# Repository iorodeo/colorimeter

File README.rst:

Colorimeter
-----------

Design files, software and firmware for IO Rodeos's open source (hardware &
software) scientific colorimeter kit for educators, students and DIY
scientists. Colorimeters are analytical devices commonly used in science labs to measure
the concentration of a solution from its light absorbing properties.
Colorimeters are extremely useful and flexible lab instruments for a wide range
of science education labs. 

This packages contains:

* Design files for the colorimeter Electronic Kicad) and Mechanical (py2scad) components.

* Arduino firmware and Python serial library for communicating the colorimeter.  

* A suite of software (w/GUI) for taking measurements with the colorimeter - e.g. 
  measuring transmittance and absorbance, generating standard curves, and  measuring 
  the concentration of solutions.

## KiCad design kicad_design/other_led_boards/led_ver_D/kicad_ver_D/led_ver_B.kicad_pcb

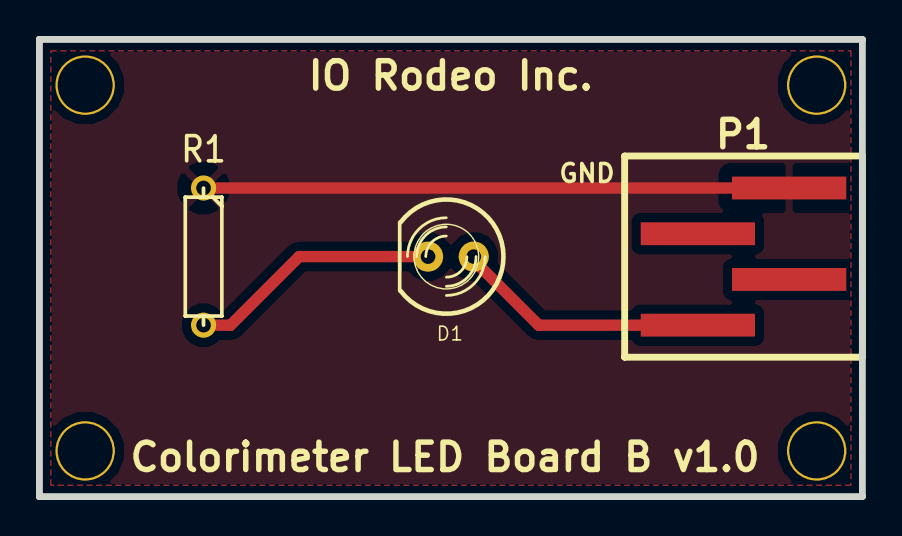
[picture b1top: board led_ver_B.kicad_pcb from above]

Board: 2 copper layers, 45.7 x 25.4 mm, 7 parts (0 on the bottom side), 3 nets.

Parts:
D1: LED; LED-5MM
M1, M2, M3, M4: MOUNT_HOLE_4_40
P1: CONN_4; smt
R1: 40; R3

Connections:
/Blue: D1.1, P1.1
GND: P1.4, R1.1
unnamed: D1.2, R1.2

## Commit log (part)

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2011-12-31 Project creation.
2011-12-31 Added firmware.
2012-01-04 New rgb led design.
2012-01-05 Added Kicad design for the Arduino shield for the colorimeter.
2012-01-07 Added KiCad footprints for two surface mount components.
2012-01-10 Finished designing Arduino shield PCB for the colorimeter.
2012-01-11 Created new version 1.1 of the color sensor PCB. New version has a 5x2 header replacing the 6x2 header. Routed the shield board and re-routed sensor v1.1. Created gerber files.
2012-01-12 Added BOMs for all three boards.
2012-01-14 Enclosure changes - resized holes and added cuvette holder.
2012-01-17 Worked on the enclosure designs. Started to add in the new sliding cover.
2012-01-17 Worked on Colorimeter class.
2012-01-18 Worked on py2scad enclosure design.
2012-01-18 Worked on colorimeter class. Finished getFrequency and getTransmission methods.
2012-01-19 Finished version 2 of the new colorimenter enclosure design.
2012-01-20 Finished writing absorbance calculation. Next up calibration.
2012-01-27 Added white channel. Worked on calbiration.
2012-01-30 Minor work on colorimeter. Played around to see if I could get LCD to stop flashing when the colorimeter take measurements.
2012-02-01 Finished Colorimeter class. Preliminary test suggest that it is working.
2012-02-02 Added class template for colorimeter data.
2012-02-02 Started working on SerialHandler class for handling serial communications with host computer.
2012-02-03 Finished serial interface - both for firmware and host. Wrote a simple gui for working with the device.
2012-02-03 Added IO pins for arduino uno shield.
2012-02-03 Created python package for colorimeter serial interface.
2012-02-04 Minor changes to python software.
2012-02-06 Added firmware test functions.
2012-02-07 Fixed bug in firmware which caused white values to be the same as the red values. Added color selection checkboxes to GUI. Added number of samples line edit to GUI.
2012-02-10 Changes to the sensor and LED boards to replace the terminal blocks with surface mount components.
2012-02-10 Version 2 of the colorimeter. Removed alot of the components that are not necessary to make a very basic breakout board.
2012-02-10 version 2p0 gerber files for sensor, led and shield boards.
2012-02-11 New project: Nano colorimeter shield
2012-02-15 Fixed design bugs. Still need to remake dxf files, etc.
2012-02-15 Added kicad missing kicad modules.
2012-03-03 Modified both sensor and LED boards to a new surface mount 4-pin male header instead of the poke home connectors. New gerber files v2p1 for both boards.
2012-03-19 Fixed spelling error on GUI text label.
2012-03-21 Added an annotated parts list for the enclosure.
2012-03-21 Added a new file for the concentration GUI.
2012-04-10 Added prototype of colorimater plotting GUI.
2012-04-10 Finished mockup of concentration GUI.
2012-04-17 Added parts layout for instructables.
2012-04-17 Separated plotting and concentration guis (mockups) from the other parts.
2012-04-17 Modified colorimeter_gui so that default serial port is automatically selected based on platform.
2012-05-30 Created slight offset in shrouded header hole position for sensor pcb.
2012-05-30 Modified inner panel slot position so that it is better aligned with the led and sensor.
2012-06-19 Working version of Plot GUI
2012-06-20 Modified colorimeter plot gui so that matplotlib backend is specified.
2012-06-20 Worked on packaging of python serial interface and various GUI's.
2012-06-20 Added temporary work around to figlegend issue on the plotting gui.
2012-06-25 Added silk screen markings to the arduino sheild. Changed the silk screen marking on the LED board - modified version number.
2012-06-25 Modified inner panel LED cable hole size. Remade laser cutting files. Restructured project file slightly.
2012-06-27 Modified firmware so that it works with Arduion versions both > 1.0 and < 1.0.
2012-07-02 Worked on measurement GUI.
2012-07-02 Further work on measurement gui.
2012-07-04 Work on measurement GUI. Added ability to test solution data from the default and user directories.
2012-07-04 Worked on context menus for tablewidget and copy, delete, edit functionality.
2012-07-05 Work on ploting function for measurement GUI.
2012-07-05 Cleaned up a a bit.
2012-07-06 Worked on ctl-c and context menu functionality for measurement GUI data tables. Fixed issue with basic GUI plotting.
2012-07-06 Modified fit used in colorimeter plot GUI so that it is constained to go through zero.
2012-07-07 Worked on measurement GUI plotting. Added live updating of plot - to new measurements and update of sample labels. Added computation of test solution coefficients from data files. Worked on delete fu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
2012-07-15 Worked on measurement and plotting gui. Added validator to plotting gui data table. Added pkg_resource stuff to measurement software - so that data files are found properly.
2012-07-16 Worked on export/import for test solution data sets.
2012-07-16 Worked on import/export of data sets.
2012-07-16 Worked on data import export. Fixed some issues with widget enable order on plot GUI.
2012-07-16 More work on export/import between plotting gui and measurement gui.
2012-07-16 Turned off development (fake it) mode for plotting gui.
2012-07-16 Modified how test solutions will be edited for both measurement and plot (standard curve) GUIs.
2012-07-16 Added led to data saved by plot and measurement GUI. LED is also now set when data is loaded into the plot GUI.
2012-07-17 Worked on unifiying handling of the data table widgets used in the plot and measurement GUIs.
2012-07-18 Worked on unifying the colorimeter GUI components.
2012-07-19 Worked on unifying the plotting and measurement GUIs.
2012-07-19 Further work on unifying the plotting and measurement programs.
2012-07-20 Worked on basic program. Fixed some issues with bar chart as it didn't reflect the current led selection. Made it so that bar chart updates with any changes to GUI and closes when GUI is closed.
2012-07-24 Work on all three programs - basic, plot, and measurement. Fixed issues with serial interface. Made modifications to firmware - so that errors can be more easily caught.
2012-07-24 Work on unifying basic program with the plotting and measuremnt programs.
2012-07-24 Further work on unify the basic program with the other two - plotting and measurement. Some minor changes to the device firmware.
2012-07-24 Finished unifying the basic program with the plotting and measurement programs.
2012-07-24 Started rearranging directory structure.
2012-07-24 More changes to python package sturcture.
2012-07-24 More work rearranging python package.
2012-07-25 Worked on test solution dialog.
2012-07-25 Finished test solution edit and import dialogs.
2012-07-25 Worked on auto creation of user data directory.
2012-07-26 Finished adding automatic user data directory creation.
2012-07-26 Fixed issue with setup.py.
2012-07-26 Moved setting of matplotlib backend to single module.
2012-07-26 Fixed issue with package_data in setup.py file.
2012-07-26 Fixed issue with starting position on windows.
2012-07-26 Added default test solutions.
2012-07-26 Modified so that default test solutions show up in the import dialog but not in the edit dialog.
2012-07-26 Modified import export so that it will work with pyinstaller as well with setup_tools.
2012-07-26 Added About dialogs w/ version number information. Set fake measure flag to False. Prettified saving for basic program.
2012-07-26 Modified the about text message.
2012-07-26 Fixed bug which effected changing test solutions in the measurement GUI.
2012-07-27 Added startup dialog.
2012-07-27 Fixed some python packaging issues and added colorimeter-main script for starting the startup dialog.
2012-07-27 Fixed some issues with using startup dialog which cause problems on windows.
2012-07-27 Fixed issues with serial connection errors on windows.
2012-07-27 Added required libraries to project - so users don't need to deal with this.
2012-07-27 Added top level readme to project.
2012-07-27 Modified readme.
2012-07-27 Modified top level README. Modified INSTALL.txt for python package.
2012-07-27 Removed scipy as requirement from python installation instructions.
2012-09-13 Cleaned up laser cutting files.
2012-09-13 Added BOMs and clean up laser cutting files.
2012-12-19 Worked on adding a nonlinear fit to colorimeter software.
2012-12-20 Added nonlinear fitting capability to plotting and measurement programs.
2012-12-20 Added method to color sensor class to allow selecting the sensors frequency scaling. Changed the default frequency scaling from 20% to 100% to enable measurement of higher concentrations. Set python 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
2012-12-20 Added API test kit data (ammonian, nitrate, nitrite) to the default data sets.
2012-12-21 Added copy of pyinstaller .spec file for compiling stand alone binaries. Currently works with pyinstaller 1.5 haven't tested upgrade to pyinstaller 2.0.
    Added cheap hack to deal with missing item from hiddenimports in scipy hook when
    using pyinstaller.
2012-12-21 Changed name in pyinstaller .spec file.
2012-12-21 Add error dialog to measurement program for the case where the users is using a nonlinear fit and the measurement falls outside of the calibration range - basically disallow extrapolation.
2013-02-22 Added inkscape files for sled and tuxcase top.
2013-04-14 Added Kicad design files for additional LED boards. Version B (single LED) and Version C (two LEDs).
2013-04-16 Worked on added ability to handle custom single LED PCB. Updateded firmware, serial libraray, and worked on updating GUI. Basic program has been modified, still need to finish modifiying the plotting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
2013-04-21 Worked on adding new custom LED mode to plotting and measurement programs.
2013-04-21 Finished modifications to software so that the colorimeter can be used with the 'custom' LED PCB.
2013-04-24 Changed default number of samples. Fixed bug which occured when switching to custom LED mode when there was no test solution data avialable.
2013-04-25 Added lineEdit for setting number for samples to the plot and measure programs.
2013-04-26 Added significant digits options.
2013-04-26 Fixed bug in plot.py which was caused by adding significant digits option.
2013-08-29 Moved .pde to .ino
2013-08-30 Began work adding modes for using both custom led board version B and C.
2013-08-31 Worked on adding custom led option for version c pcb.
2013-09-03 Worked on adding new ver C PCB mode. Refactoring how this is handled.
2013-09-11 Added pin definitions for BLE shield.
2013-10-26 Worked on additing ability to use version c pcb to plottin program. Modified GUI and made changes so that is will at least open with the new data structures.
2013-10-26 Modified plot.py so that measurements are working with the new data structures.
2013-10-26 Finished modificatinos to plot.py so that it works with the version c pcb.
2013-10-27 Finished modifications to measure.py so that it will work with version c pcb.
2013-10-27 Fixed issue with colormode setting.
2013-12-30 Fixed bug effecting saveing and loading data sets
2013-12-31 Added raise_ after to show to various GUI apps so they come to the front in Mac OS.
2014-05-15 New version D design with PLCC 5050 LED and transistor switch for higher voltages. Note, still need to rename some files.
2014-05-15 Changed some file names.
2014-05-15 Added Gerber files for LED Ver D board.
2014-07-12 Added second cuvette size.
2014-11-08 Added new pdfs of schematics.
2015-01-22 Fixed bug which caused issues with setting the default sensorMode value to anything other than StandardRGBLED.
2016-09-05 Fixed problem with nonlinear fit. It now takes the largest contiguous bock on monotonic data after fitting.
2016-09-15 Added pH as units to plot and measurement programs.
2016-09-15 Turned off development mode.
2017-05-25 Removed LED_5050 led_5050 .bak files.
2019-01-24 Add replacement RGB LED to BOM.
2019-10-16 Finished initial upgrade to Python3 and PyQt5. Still need to test and shake out bugs.
2019-10-27 Bug fixes after port to PyQt5 and Python3.
2019-10-27 Fixed issues with test solution dialog cause by port to PyQt5 and python3.
2019-11-06 Fixed bug causing issue with loading yaml file. Bug due to newer yaml library.
2019-11-06 Changed version numbers.
